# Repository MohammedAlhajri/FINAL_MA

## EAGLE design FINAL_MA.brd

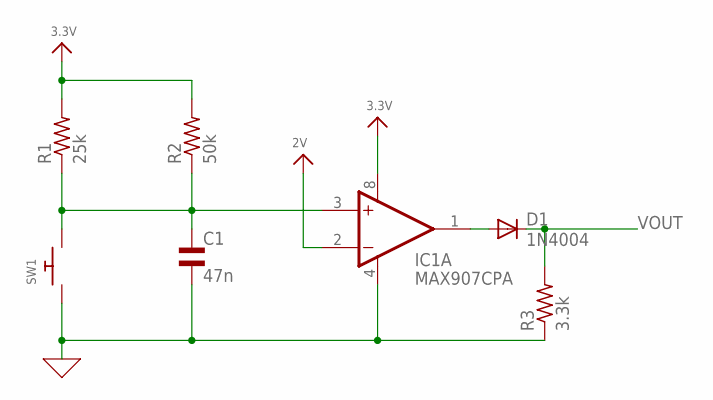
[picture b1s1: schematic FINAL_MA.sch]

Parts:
C1: 47n; EU25-10
D1: 1N4004; DO41-10
IC1: MAX907CPA; DIL08
R1: 25k; 0204/5
R2: 50k; 0204/5
R3: 3.3k; 0204/5
SW1: SWITCH_PUSHBUTTONEVQ-PE; TACT_PANA-EVQ

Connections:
0: C1.2, IC1.4 (V-), R3.1, SW1.P$1
unnamed: D1.A, IC1.1 (OUT)
unnamed: C1.1, IC1.3 (+IN), R1.1, R2.1, SW1.P$2
VCC: IC1.2 (-IN), IC1.8 (V+), R1.2, R2.2
VOUT: D1.C, R3.2

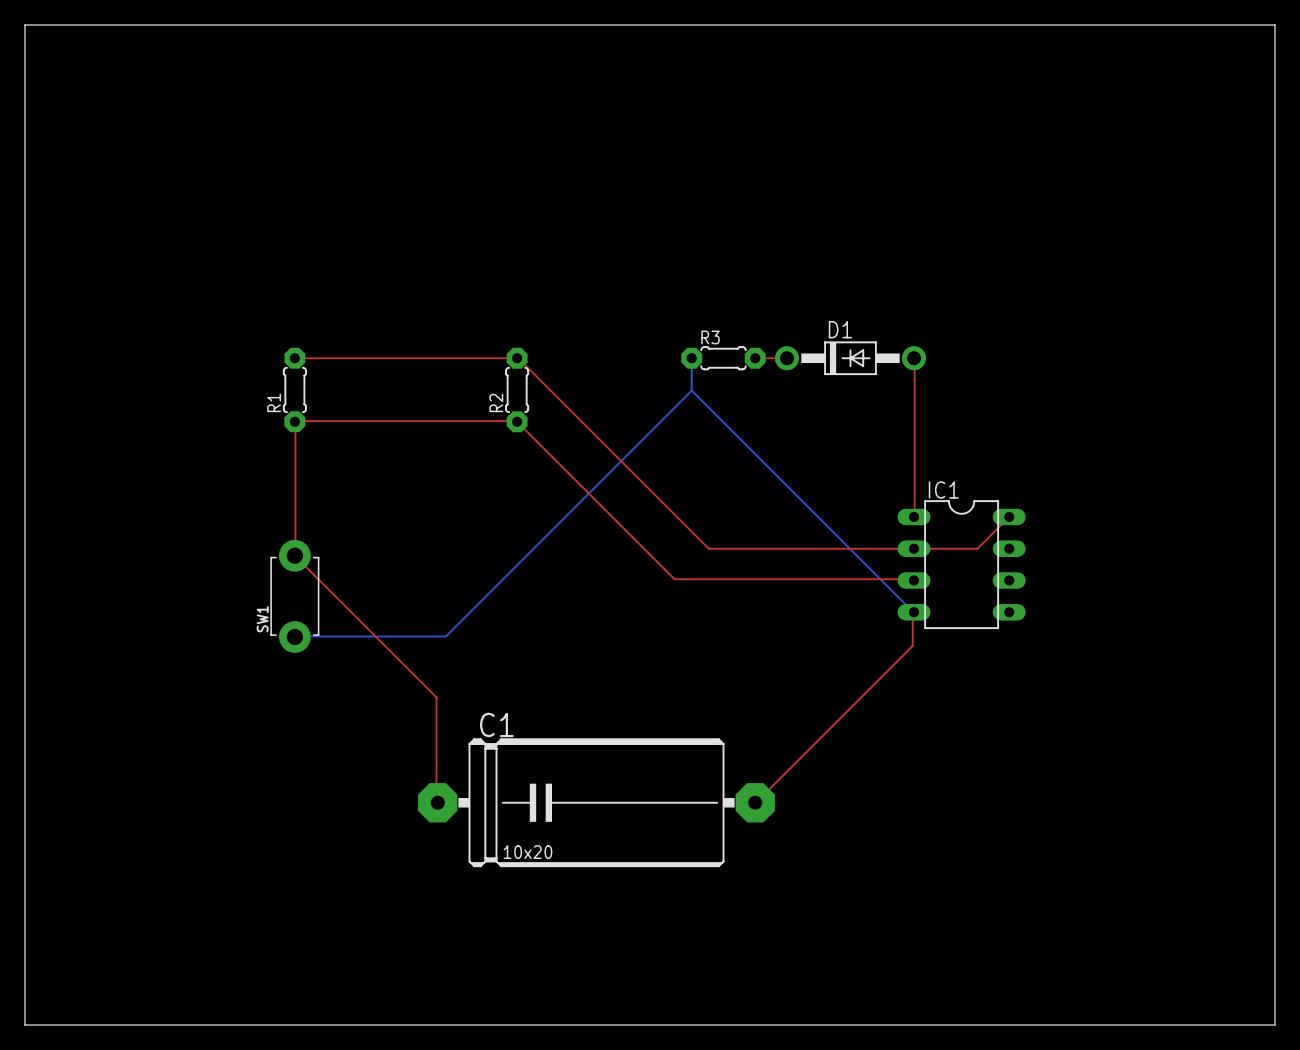
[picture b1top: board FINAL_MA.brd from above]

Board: 2 copper layers, 100.0 x 80.0 mm, 7 parts (0 on the bottom side), 5 nets.
